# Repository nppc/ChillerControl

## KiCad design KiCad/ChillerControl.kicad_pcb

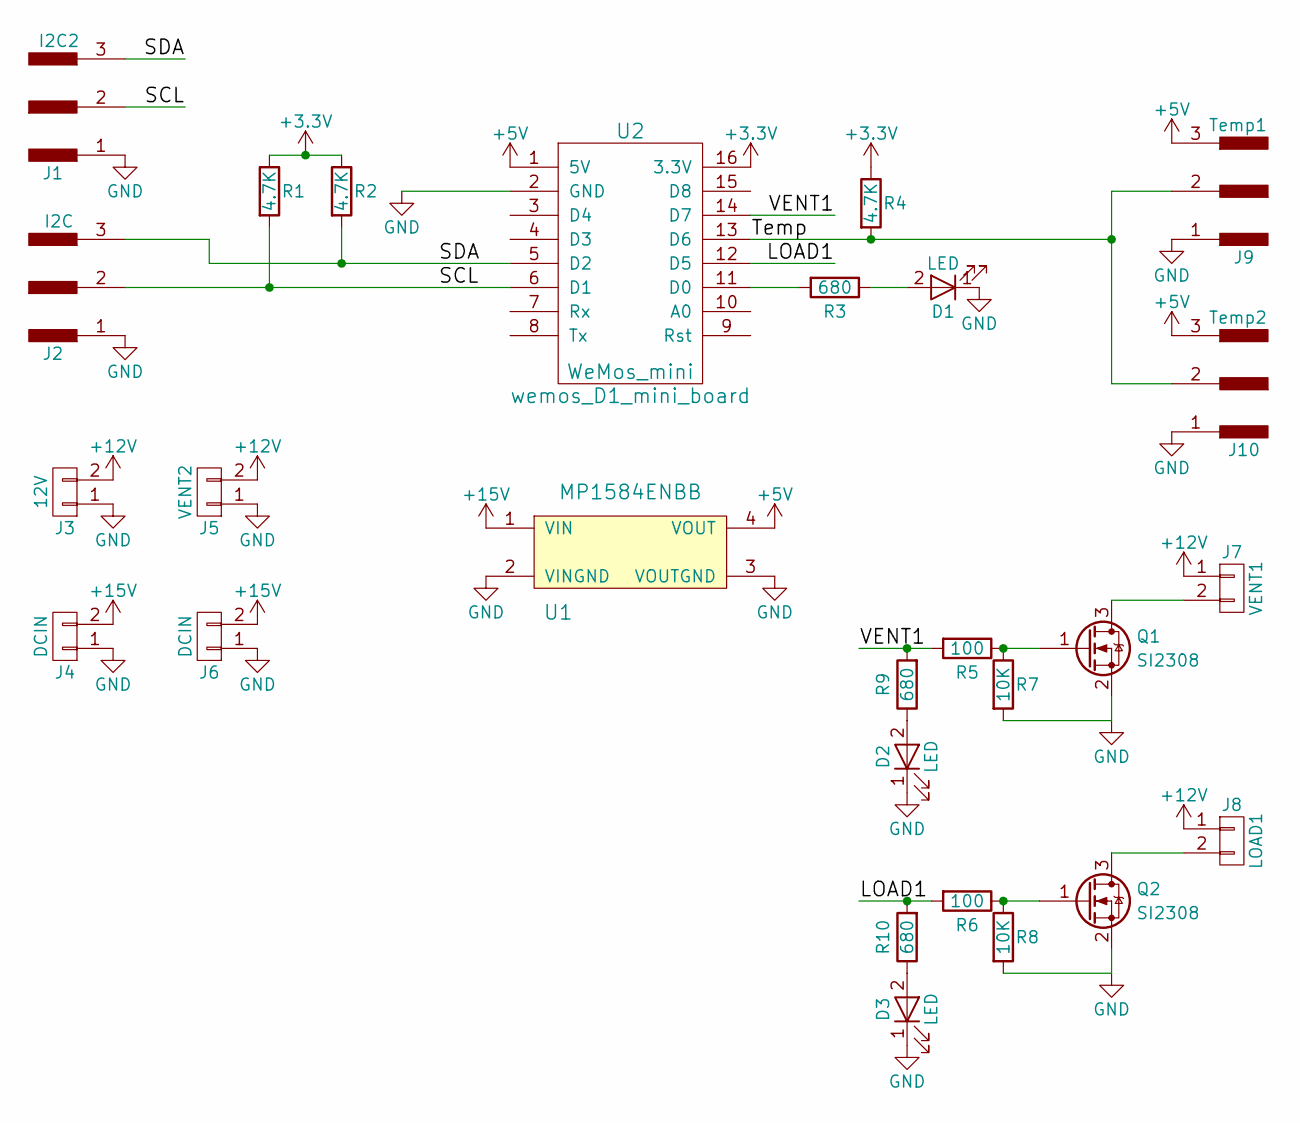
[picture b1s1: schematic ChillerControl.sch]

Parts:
D1, D2, D3: LED; LED_0805
J1: I2C2; Pin_Header_Straight_1x03_Pitch2.54mm
J2: I2C; Pin_Header_Straight_1x03_Pitch2.54mm
J3: 12V; Conn2pin_2.54mm
J4, J6: DCIN; Conn_Power
J5: VENT2; Conn2pin_2.54mm
J7: VENT1; Conn2pin_2.54mm
J8: LOAD1; Conn2pin_2.54mm
J9: Temp1; Pin_Header_Straight_1x03_Pitch2.54mm
J10: Temp2; Pin_Header_Straight_1x03_Pitch2.54mm
Q1, Q2: SI2308; SOT-23
R1, R2, R4: 4.7K; R_0603
R3, R9, R10: 680; R_0603
R5, R6: 100; R_0603
R7, R8: 10K; R_0603
U1: MP1584ENBB; MP1584_buck_module
U2: WeMos_mini; wemos_D1_mini_board

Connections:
+3V3: R1.1, R2.1, R4.1, U2.16 (3.3V)
+5V: J9.3, J10.3, U1.4 (VOUT), U2.1 (5V)
+12V: J3.2, J5.2, J7.1, J8.1
+15V: J4.2, J6.2, U1.1 (VIN)
/LOAD1: R6.2, R10.2, U2.12 (D5)
/SCL: J1.2, J2.2, R1.2, U2.6 (D1)
/SDA: J1.3, J2.3, R2.2, U2.5 (D2)
/Temp: J9.2, J10.2, R4.2, U2.13 (D6)
/VENT1: R5.2, R9.2, U2.14 (D7)
GND: D1.1 (K), D2.1 (K), D3.1 (K), J1.1, J2.1, J3.1, J4.1, J5.1, J6.1, J9.1, J10.1, Q1.2 (S), Q2.2 (S), R7.2, R8.2, U1.2 (VINGND), U1.3 (VOUTGND), U2.2 (GND)
unnamed: D1.2 (A), R3.1
unnamed: D2.2 (A), R9.1
unnamed: D3.2 (A), R10.1
unnamed: J7.2, Q1.3 (D)
unnamed: J8.2, Q2.3 (D)
unnamed: Q1.1 (G), R5.1, R7.1
unnamed: Q2.1 (G), R6.1, R8.1
unnamed: R3.2, U2.11 (D0)

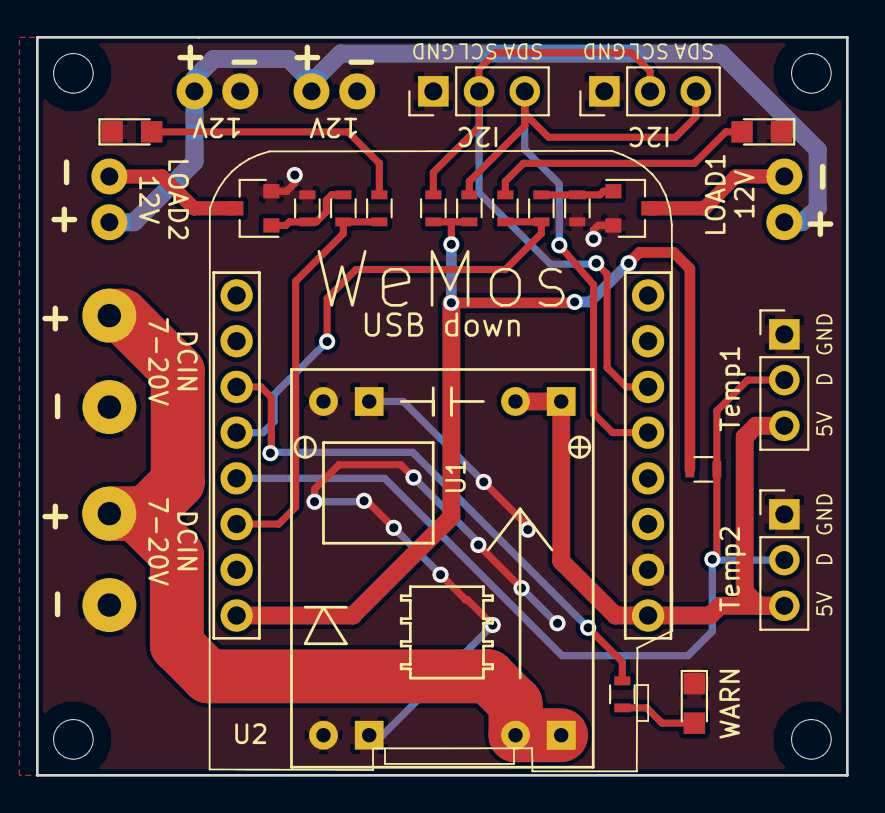
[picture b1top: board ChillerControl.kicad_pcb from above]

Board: 2 copper layers, 45.0 x 41.0 mm, 27 parts (0 on the bottom side), 18 nets.

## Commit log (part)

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2018-08-06 Initial schematic and PCB
2018-09-02 reference data
2018-09-03 Initial firmware
2018-09-04 initial version
2018-09-05 HTTP rework
2018-09-05 fix html form
2018-09-06 Added OTA http firmware update
2018-09-06 Celsius char fix
2018-09-06 Adjust safe voltage
2018-09-06 Added Settings page
2018-09-06 Added Version info
2018-09-06 Uptime format
2018-09-06 Temperature address print
2018-09-06 Fix issue with time conversion
2018-09-07 Added PID control
2018-09-07 Added PID settings
2018-09-07 PID loop control is tested and working
2018-09-07 EEPROM routines added
2018-09-07 STOP button for stopping the Buck slowly
2018-09-09 Thingspeak data sending
2018-09-10 SPIFF used for storing settings
2018-09-12 Add Network settings html page
2018-09-12 CSS loaded from SPIFF. Added simple SPIFF explorer
2018-09-14 Add json support
2018-09-14 json fix
2018-09-14 Store settings in json format
2018-09-14 added Ubidots IoT
2018-09-15 Case first iteration
2018-09-15 finalize scad project. show temp sensors
2018-09-15 implement second temperature sensor
2018-09-15 dynamic json buffer
2018-09-16 adjust fan off temp
2018-09-16 Added new value to Ubidots
2018-09-17 Prevent overheat.
2018-09-17 Request data from Buck every 2 seconds
2018-09-17 First ajax implementation
2018-09-17 Enable fan on startup
2018-09-17 V2.0 Main screen realtime update.
2018-09-19 Web FB: Confirm file delete
2018-09-19 fix for file delete confirmation
2018-09-24 SCAD lock
2018-09-28 Increase the resolution for I (4 digits after .)
2018-09-29 final version of lock
2018-10-01 I2C recheck if failed
2018-10-02 vent cover 2
2018-10-06 I2C errors count
2018-10-06 Confirm Stop action
2019-01-14 Rework Extreme temp protection
2019-01-14 Store DC/DC settings outside of DC/DC
2019-01-14 New Debug webpage for replies from IoT.
2019-01-14 Try to make WIFI connection more robust
2019-01-14 fix typo in Extrme temp detection
2019-01-25 Implement control via UbiDots
2019-02-05 Change temperature via Ubidots
2019-02-06 More robust data receiving from IoT
2019-02-06 fix stopping display issue
2019-02-06 Dynamically display setTemp value on main page
2019-02-06 Enable/Disable Dynamic Fan Control
2019-03-08 Add heating mode. Config
2019-03-09 Implement heating control
2019-03-10 Implement heating control 2
2019-03-11 interface fix. fan control fix
2019-03-11 fix old issue with stopping display
2019-03-11 Send hot pwm to IoT
2019-03-12 Alfa version of heat/cool version
2019-03-12 working version of hot/cold control
2019-03-13 some minor fix for http requests process
2019-03-15 adjust mixed mode logic
2019-03-16 fix transition between heat/cool
2019-03-18 fix transition between heat/cool 2
2019-03-20 Implement Dynamic shange of set temperature
2019-03-20 Dynamic temperature working
2019-03-21 recalculate hot pwm value for ubidots
2019-03-22 Rework IoT connection to be more reliable
2019-03-22 get rid off SPIFFS to check will it resolve hangs
2019-03-22 add dynamictempsetting
2019-03-22 fix css and script file load
2019-03-22 Implement HTMLDebug Object
2019-03-23 Fix hot fan control while heating
2019-03-25 Introduce dynamicTempDiffCoeff
2021-11-08 Fix set temperature for heating
